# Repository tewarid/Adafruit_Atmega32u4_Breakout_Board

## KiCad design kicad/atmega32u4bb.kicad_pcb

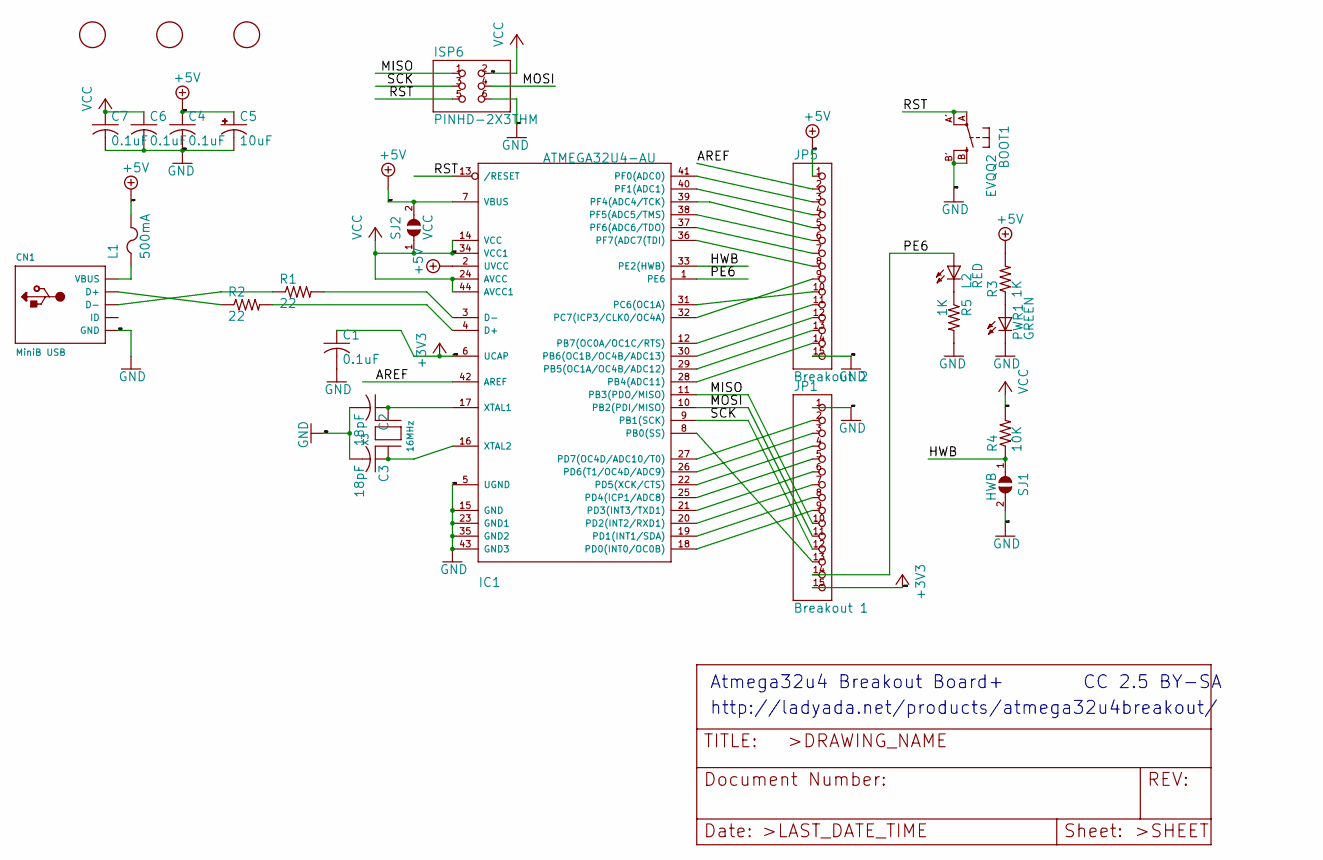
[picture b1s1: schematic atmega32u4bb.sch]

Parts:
BOOT1: EVQQ2; EVQ-Q2
C1, C4, C6, C7: 0.1uF; C0805K
C2, C3: 18pF; C0805K
C5: 10uF; A_3216-18R
CN1: MiniB USB; USB-MINIB
IC1: ATMEGA32U4-AU; TQFP44
ISP6: PINHD-2X3THM; ISP6
JP1: Breakout 1; 1X15-CB
JP5: Breakout 2; 1X15-CB
L1: 500mA; R1206
L2: RED; CHIPLED_0805
PWR1: GREEN; CHIPLED_0805
R1, R2: 22; R0805
R3, R5: 1K; R0805
R4: 10K; R0805
SJ1: HWB; SJ
SJ2: VCC; SJ
U$1, U$2, U$6: FIDUCIAL; FIDUCIAL_1MM
X3: 16MHz; NX5032

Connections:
+3V3: C1.1, IC1.6 (UCAP), JP1.15
+5V: C4.1, C5.+, IC1.2 (UVCC), IC1.7 (VBUS), JP5.1, L1.2, R3.2, SJ2.2
/AREF: IC1.42 (AREF), JP5.2
/HWB: IC1.33 (PE2(HWB)), R4.1, SJ1.1
/MISO: IC1.11 (PB3(PDO/MISO)), ISP6.1, JP1.10
/MOSI: IC1.10 (PB2(PDI/MISO)), ISP6.4, JP1.11
/PE6: IC1.1 (PE6), JP1.14, L2.A
/RST: BOOT1.A, BOOT1.A' (P1), IC1.13 (/RESET), ISP6.5
/SCK: IC1.9 (PB1(SCK)), ISP6.3, JP1.12
GND: BOOT1.B (S), BOOT1.B' (S1), C1.2, C2.2, C3.2, C4.2, C5.-, C6.2, C7.2, CN1.GND, IC1.5 (UGND), IC1.15 (GND), IC1.23 (GND1), IC1.35 (GND2), IC1.43 (GND3), ISP6.6, JP1.1, JP5.15, PWR1.C, R5.2, SJ1.2
unnamed: C2.1, IC1.17 (XTAL1), X3.P$2
unnamed: C3.1, IC1.16 (XTAL2), X3.P$1
unnamed: CN1.D+, R2.1
unnamed: CN1.D-, R1.1
unnamed: CN1.VBUS, L1.1
unnamed: IC1.3 (D-), R1.2
unnamed: IC1.4 (D+), R2.2
unnamed: IC1.8 (PB0(SS)), JP1.13
unnamed: IC1.12 (PB7(OC0A/OC1C/RTS)), JP5.11
unnamed: IC1.18 (PD0(INT0/OC0B)), JP1.9
unnamed: IC1.19 (PD1(INT1/SDA)), JP1.8
unnamed: IC1.20 (PD2(INT2/RXD1)), JP1.7
unnamed: IC1.21 (PD3(INT3/TXD1)), JP1.6
unnamed: IC1.22 (PD5(XCK/CTS)), JP1.4
unnamed: IC1.25 (PD4(ICP1/ADC8)), JP1.5
unnamed: IC1.26 (PD6(T1/OC4D/ADC9)), JP1.3
unnamed: IC1.27 (PD7(OC4D/ADC10/T0)), JP1.2
unnamed: IC1.28 (PB4(ADC11)), JP5.14
unnamed: IC1.29 (PB5(OC1A/OC4B/ADC12)), JP5.13
unnamed: IC1.30 (PB6(OC1B/OC4B/ADC13)), JP5.12
unnamed: IC1.31 (PC6(OC1A)), JP5.10
unnamed: IC1.32 (PC7(ICP3/CLK0/OC4A)), JP5.9
unnamed: IC1.36 (PF7(ADC7(TDI)), JP5.8
unnamed: IC1.37 (PF6(ADC6/TDO)), JP5.7
unnamed: IC1.38 (PF5(ADC5/TMS)), JP5.6
unnamed: IC1.39 (PF4(ADC4/TCK)), JP5.5
unnamed: IC1.40 (PF1(ADC1)), JP5.4
unnamed: IC1.41 (PF0(ADC0)), JP5.3
unnamed: L2.C, R5.1
unnamed: PWR1.A, R3.1
VCC: C6.1, C7.1, IC1.14 (VCC), IC1.24 (AVCC), IC1.34 (VCC1), IC1.44 (AVCC1), ISP6.2, R4.2, SJ2.1

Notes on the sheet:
Atmega32u4 Breakout Board+
http://ladyada.net/products/atmega32u4breakout/
CC 2.5 BY-SA

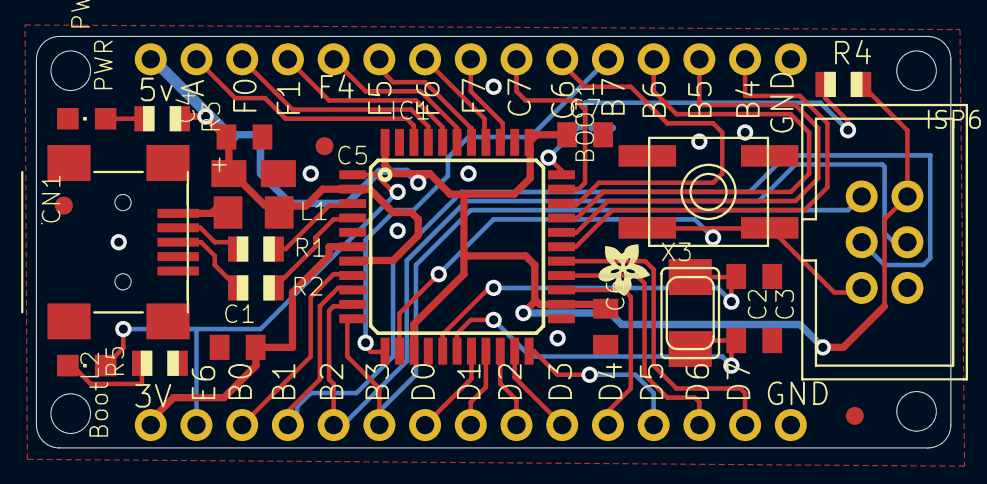
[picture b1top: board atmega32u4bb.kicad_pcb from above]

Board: 16 copper layers, 50.8 x 22.9 mm, 32 parts (0 on the bottom side), 41 nets.

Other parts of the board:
@HOLE0, @HOLE1, @HOLE2, @HOLE3: (no value)
U$4: ADAFRUIT200MIL

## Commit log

2021-02-25 convert pcb to eagle xml format
2021-02-25 add kicad pcb
